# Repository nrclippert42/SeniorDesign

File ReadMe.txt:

This is a repository! They rock!! Now I am changing this file.
And now a new line!

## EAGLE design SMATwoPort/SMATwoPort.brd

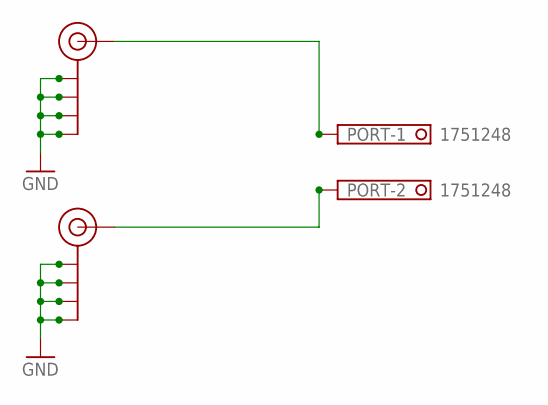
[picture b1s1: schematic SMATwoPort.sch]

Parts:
J$1, J$2: SMA_EDGE; SMA-EDGE
PORT: 1751248

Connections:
GND: J$1.GND@0 (GND), J$1.GND@1 (GND), J$1.GND@2 (GND), J$1.GND@3 (GND), J$2.GND@0 (GND), J$2.GND@1 (GND), J$2.GND@2 (GND), J$2.GND@3 (GND)
unnamed: J$2.SIG (SIGNAL), PORT.1
unnamed: J$1.SIG (SIGNAL), PORT.2

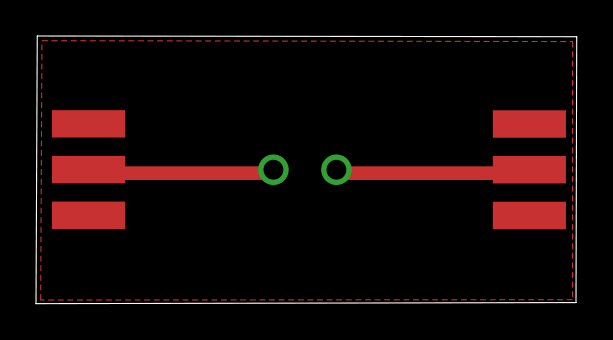
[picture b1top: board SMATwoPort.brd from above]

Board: 2 copper layers, 30.0 x 14.9 mm, 3 parts (1 on the bottom side), 3 nets.

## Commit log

2015-03-24 Initial Checkin
2015-03-26 Added previously used files
2015-03-28 This is a description
2015-03-28 This is another description
2015-04-27 Add some Matlab plotting scripts
2015-04-27 a2d first edition
2015-04-30 Removed files that were unneeded or save else where. Added real time plotting gui.
2015-05-04 Got the data collection gui working. ... More updates coming
2015-05-07 Added some error checking and an input selection Added auto axis scaling Added the data sketch I used just in case
2015-05-07 Began adding save functionality
2015-05-11 small modifications including timing and button disable and baudrate
2015-08-31 Added documents from last semester
2015-09-01 Added Design 3 assignment
2015-09-08 Updated according to new direction where we don't have to build a PCB
2015-09-08 changed need to required in requirement 1 and removed requirement number 6
2015-09-21 Added SMA eagle files and model. Cleaned up unneeded files.
2015-09-21 First upload of research paper
2015-09-29 add holes for wires on test fixture, sized the "beaker to 12.5mm" and added junctions to eagle schematic
2015-09-29 Scaled SMAboard model to actual size. Added a combined model with the plate holder and SMAboard.
2015-10-02 Added Pictures to the TMP Paper
2015-10-02 redone output for test fixture
2015-10-02 added pictures of our fixture for documentation
2015-10-05 Resized micrometer hole
2015-10-05 added section about implications of TMP.
2015-10-05 Added micometer cap model to the repo.
2015-10-31 Updated pcb to have sma's on the side to accommodate Network Analyzer cables.
2015-11-02 fixed the test fixture to have a seperate beaker.
2015-11-02 fixed document to current research approach.
2015-11-03 fixed pictures to newer version
2015-11-10 started procedure
2015-11-10 added procedure for cell handling
2015-11-10 Added SParameter data
2015-11-12 added document for network analyzer
2015-11-12 added documents for the network analyzer.
2015-11-12 added s parameter description.
2015-11-14 added s parameters and references
2015-11-15 Added data files and matlab workspaces with data. Added matlab scripts that were used during data manipulation
2015-11-15 added z parameter model
2015-11-17 pushed Matlab stuff
2015-11-17 added potential section
2015-11-18 Adjusting generation of permittivity and conductivity
2015-11-18 added conclusion paragraph
2015-11-19 fixed area of a circle equation
2015-11-19 add ;
2015-11-19 fixed impedance calculations
2015-11-20 added research documents
2015-11-20 Added impedance data
2015-11-20 fixed permittivity problem
2015-11-21 Added poster to repo and removed unused folder
2015-11-21 Added a few things to the poster to test out manipulation
2015-11-21 edited errors in the documents
2015-11-22 Revert "edited errors in the documents"
    This reverts commit 7b5aba0abfd10e075658d2641c99c9f7d9a5320d.
    Conflicts:
    TMP Paper/Measuring Transmembrane Potential of Synthetic Cells in RF.aux
    TMP Paper/Measuring Transmembrane Potential of Synthetic Cells in RF.log
    TMP Paper/Measuring Transmembrane Potential of Synthetic Cells in RF.out
2015-11-22 Found the correct version of the paper source
2015-11-22 fixed the horrible mess I created

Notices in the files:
parts and their libraries:
sparkfun-connectors: Licensing: Creative Commons ShareAlike 4.0 International - https://creativecommons.org/licenses/by-sa/4.0
